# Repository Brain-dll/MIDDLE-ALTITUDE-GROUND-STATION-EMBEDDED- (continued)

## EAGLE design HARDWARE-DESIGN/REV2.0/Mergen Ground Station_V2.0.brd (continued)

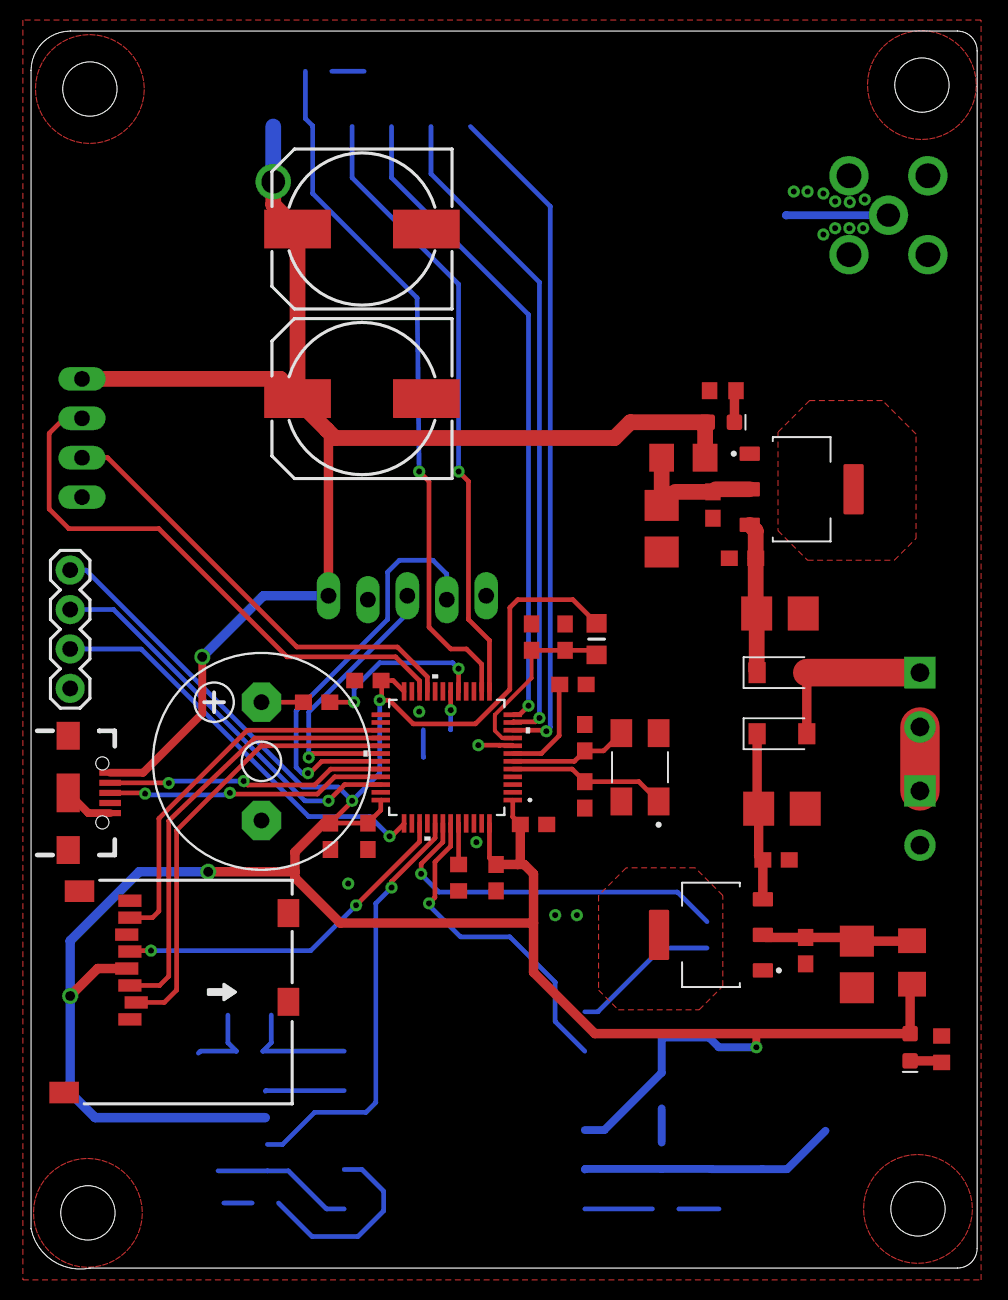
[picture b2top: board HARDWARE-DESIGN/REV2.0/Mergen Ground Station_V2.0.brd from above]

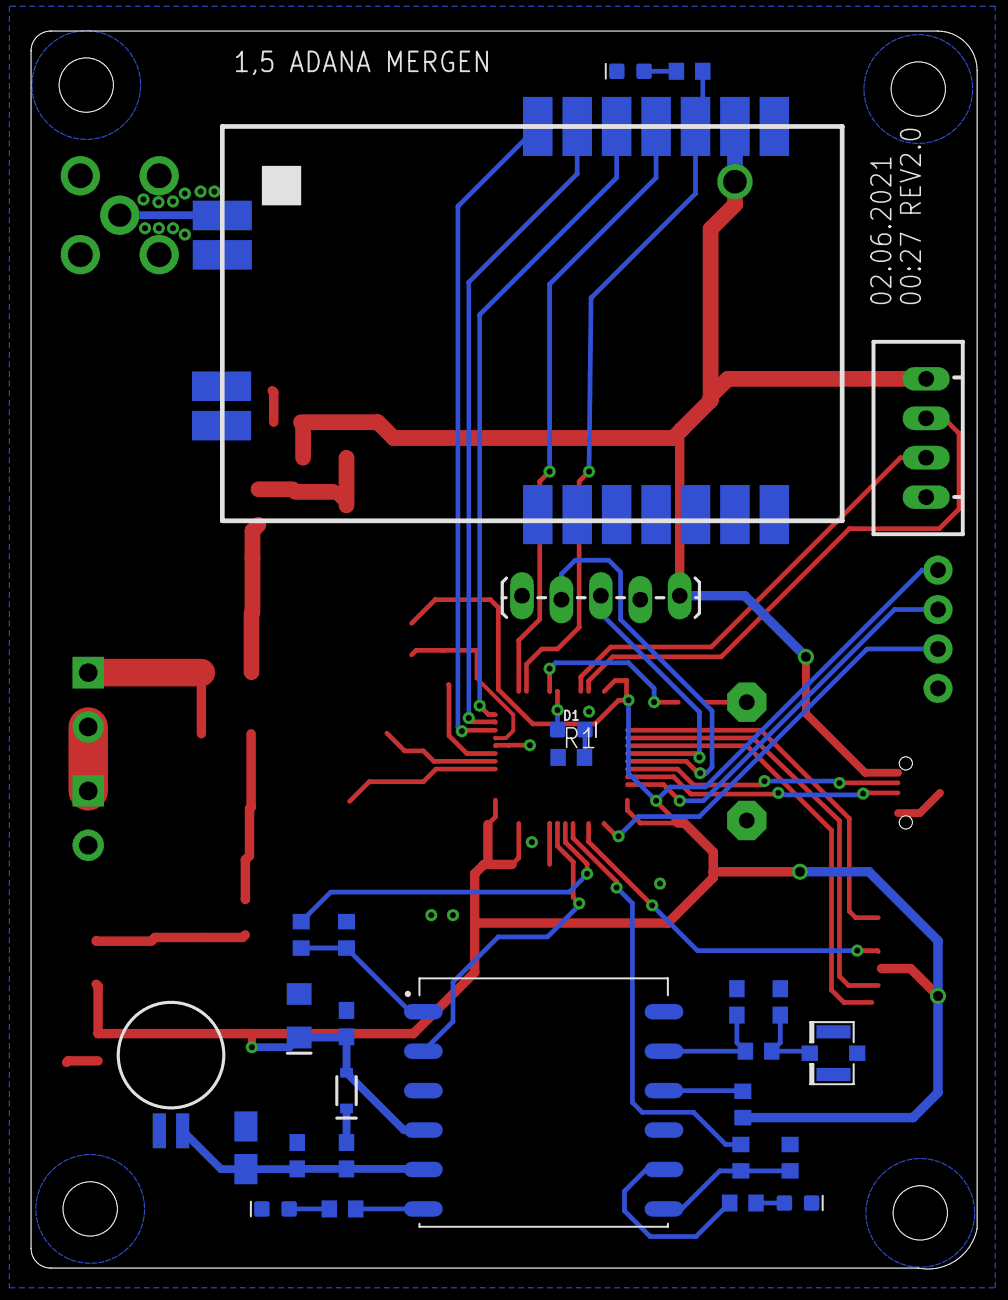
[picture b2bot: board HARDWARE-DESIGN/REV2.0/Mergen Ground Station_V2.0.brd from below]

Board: 2 copper layers, 60.9 x 79.7 mm, 70 parts (31 on the bottom side), 53 nets.

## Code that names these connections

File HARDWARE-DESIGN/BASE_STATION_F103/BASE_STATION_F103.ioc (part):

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Mcu.Name=STM32F103C(8-B)Tx
Mcu.Package=LQFP48
Mcu.UserName=STM32F103C8Tx
PA0-WKUP.GPIOParameters=GPIO_Label
PA0-WKUP.GPIO_Label=M0
PA0-WKUP.Signal=GPIO_Output
PA1.GPIOParameters=GPIO_Label
PA1.GPIO_Label=M1
PA1.Signal=GPIO_Output
PA10.Mode=Asynchronous
PA10.Signal=USART1_RX
PA13.Mode=Serial_Wire
PA13.Signal=SYS_JTMS-SWDIO
PA14.Mode=Serial_Wire
PA14.Signal=SYS_JTCK-SWCLK
PA2.Mode=Asynchronous
PA2.Signal=USART2_TX
PA3.Mode=Asynchronous
PA3.Signal=USART2_RX
PA7.GPIOParameters=GPIO_Label
PA7.GPIO_Label=LED2
PA7.Signal=GPIO_Output
PA9.Mode=Asynchronous
PA9.Signal=USART1_TX
PB0.GPIOParameters=GPIO_Label
PB0.GPIO_Label=LED
PB0.Signal=GPIO_Output
PB10.Mode=Asynchronous
PB10.Signal=USART3_TX
PB11.Mode=Asynchronous
PB11.Signal=USART3_RX
PB12.GPIOParameters=GPIO_Label
PB12.GPIO_Label=SDCARD_CS
PB12.Signal=GPIO_Output
PB13.Mode=Full_Duplex_Master
PB13.Signal=SPI2_SCK
PB14.Mode=Full_Duplex_Master
PB14.Signal=SPI2_MISO
PB15.Mode=Full_Duplex_Master
PB15.Signal=SPI2_MOSI
PB4.GPIOParameters=GPIO_Label
PB4.GPIO_Label=BUZZER
PB4.Signal=GPIO_Output
PB6.Mode=I2C
PB6.Signal=I2C1_SCL
PB7.Mode=I2C
PB7.Signal=I2C1_SDA
PD0-OSC_IN.Mode=HSE-External-Oscillator
PD0-OSC_IN.Signal=RCC_OSC_IN
PD1-OSC_OUT.Mode=HSE-External-Oscillator
PD1-OSC_OUT.Signal=RCC_OSC_OUT
RCC.SYSCLKFreq_VALUE=72000000
RCC.SYSCLKSource=RCC_SYSCLKSOURCE_PLLCLK
board=custom

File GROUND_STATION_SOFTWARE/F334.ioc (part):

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Mcu.Name=STM32F334C(4-6-8)Tx
Mcu.Package=LQFP48
Mcu.UserName=STM32F334C8Tx
PA0.GPIOParameters=GPIO_Label
PA0.GPIO_Label=M0
PA0.Signal=GPIO_Output
PA1.GPIOParameters=GPIO_Label
PA1.GPIO_Label=M1
PA1.Signal=GPIO_Output
PA10.Mode=Asynchronous
PA10.Signal=USART1_RX
PA13.Mode=Serial_Wire
PA13.Signal=SYS_JTMS-SWDIO
PA14.Mode=Serial_Wire
PA14.Signal=SYS_JTCK-SWCLK
PA2.Mode=Asynchronous
PA2.Signal=USART2_TX
PA3.Mode=Asynchronous
PA3.Signal=USART2_RX
PA7.GPIOParameters=GPIO_Label
PA7.GPIO_Label=LED2
PA7.Signal=GPIO_Output
PA9.Mode=Asynchronous
PA9.Signal=USART1_TX
PB0.GPIOParameters=GPIO_Label
PB0.GPIO_Label=LED
PB0.Signal=GPIO_Output
PB10.Mode=Asynchronous
PB10.Signal=USART3_TX
PB11.Mode=Asynchronous
PB11.Signal=USART3_RX
PB4.GPIOParameters=GPIO_Label
PB4.GPIO_Label=BUZZER
PB4.Signal=GPIO_Output
PB6.Mode=I2C
PB6.Signal=I2C1_SCL
PB7.Mode=I2C
PB7.Signal=I2C1_SDA
PF0\ /\ OSC_IN.Mode=HSE-External-Oscillator
PF0\ /\ OSC_IN.Signal=RCC_OSC_IN
PF1\ /\ OSC_OUT.Mode=HSE-External-Oscillator
PF1\ /\ OSC_OUT.Signal=RCC_OSC_OUT
RCC.HSEPLLFreq_Value=8000000
RCC.HSE_VALUE=8000000
RCC.SYSCLKFreq_VALUE=72000000
RCC.SYSCLKSourceVirtual=RCC_SYSCLKSOURCE_PLLCLK
board=custom

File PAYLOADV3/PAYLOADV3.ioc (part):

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Mcu.Name=STM32F103C(8-B)Tx
Mcu.Package=LQFP48
Mcu.UserName=STM32F103C8Tx
PA13.Mode=Serial_Wire
PA13.Signal=SYS_JTMS-SWDIO
PA14.Mode=Serial_Wire
PA14.Signal=SYS_JTCK-SWCLK
PA2.Mode=Asynchronous
PA2.Signal=USART2_TX
PA3.Mode=Asynchronous
PA3.Signal=USART2_RX
PA7.GPIOParameters=GPIO_Label
PA7.GPIO_Label=LED
PA7.Signal=GPIO_Output
PA8.GPIOParameters=GPIO_Label
PA8.GPIO_Label=SD_CS
PA8.Signal=GPIO_Output
PB0.GPIOParameters=GPIO_Label
PB0.GPIO_Label=BUZZER
PB0.Signal=GPIO_Output
PB13.Mode=Full_Duplex_Master
PB13.Signal=SPI2_SCK
PB14.Mode=Full_Duplex_Master
PB14.Signal=SPI2_MISO
PB15.Mode=Full_Duplex_Master
PB15.Signal=SPI2_MOSI
PB6.Mode=Asynchronous
PB6.Signal=USART1_TX
PB7.Mode=Asynchronous
PB7.Signal=USART1_RX
PB8.Mode=I2C
PB8.Signal=I2C1_SCL
PB9.Mode=I2C
PB9.Signal=I2C1_SDA
PD0-OSC_IN.Mode=HSE-External-Oscillator
PD0-OSC_IN.Signal=RCC_OSC_IN
PD1-OSC_OUT.Mode=HSE-External-Oscillator
PD1-OSC_OUT.Signal=RCC_OSC_OUT
RCC.SYSCLKFreq_VALUE=72000000
RCC.SYSCLKSource=RCC_SYSCLKSOURCE_PLLCLK
board=custom

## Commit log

2021-04-03 Polygon witdh was increased IMPOTANT**
2021-04-03 Polygon 15 mils
2021-04-06 Terminal Blocks were changed
2021-04-08 packages was modified according to stock situation
2021-04-19 Some modification was done
2021-05-03 Design was been modified by Osman, and component name locations was arranged
2021-06-02 Ground station V2.0 released by brain.dll
2021-06-14 Version 3.0 was relased by brain.dll
2021-06-15 new buzzer was added
2021-06-30 VDDA cap value was changed
2021-07-05 Lora configuration connectors were added
2021-08-11 Sofware Update
2021-08-15 Software was updated
2021-08-31 Last updates was completed, Ready for flying
2021-09-01 Nextion documents was uploaded
2021-09-17 Systems are stable
